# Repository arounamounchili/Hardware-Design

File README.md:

# Hardware-Design
All my PCB design projects

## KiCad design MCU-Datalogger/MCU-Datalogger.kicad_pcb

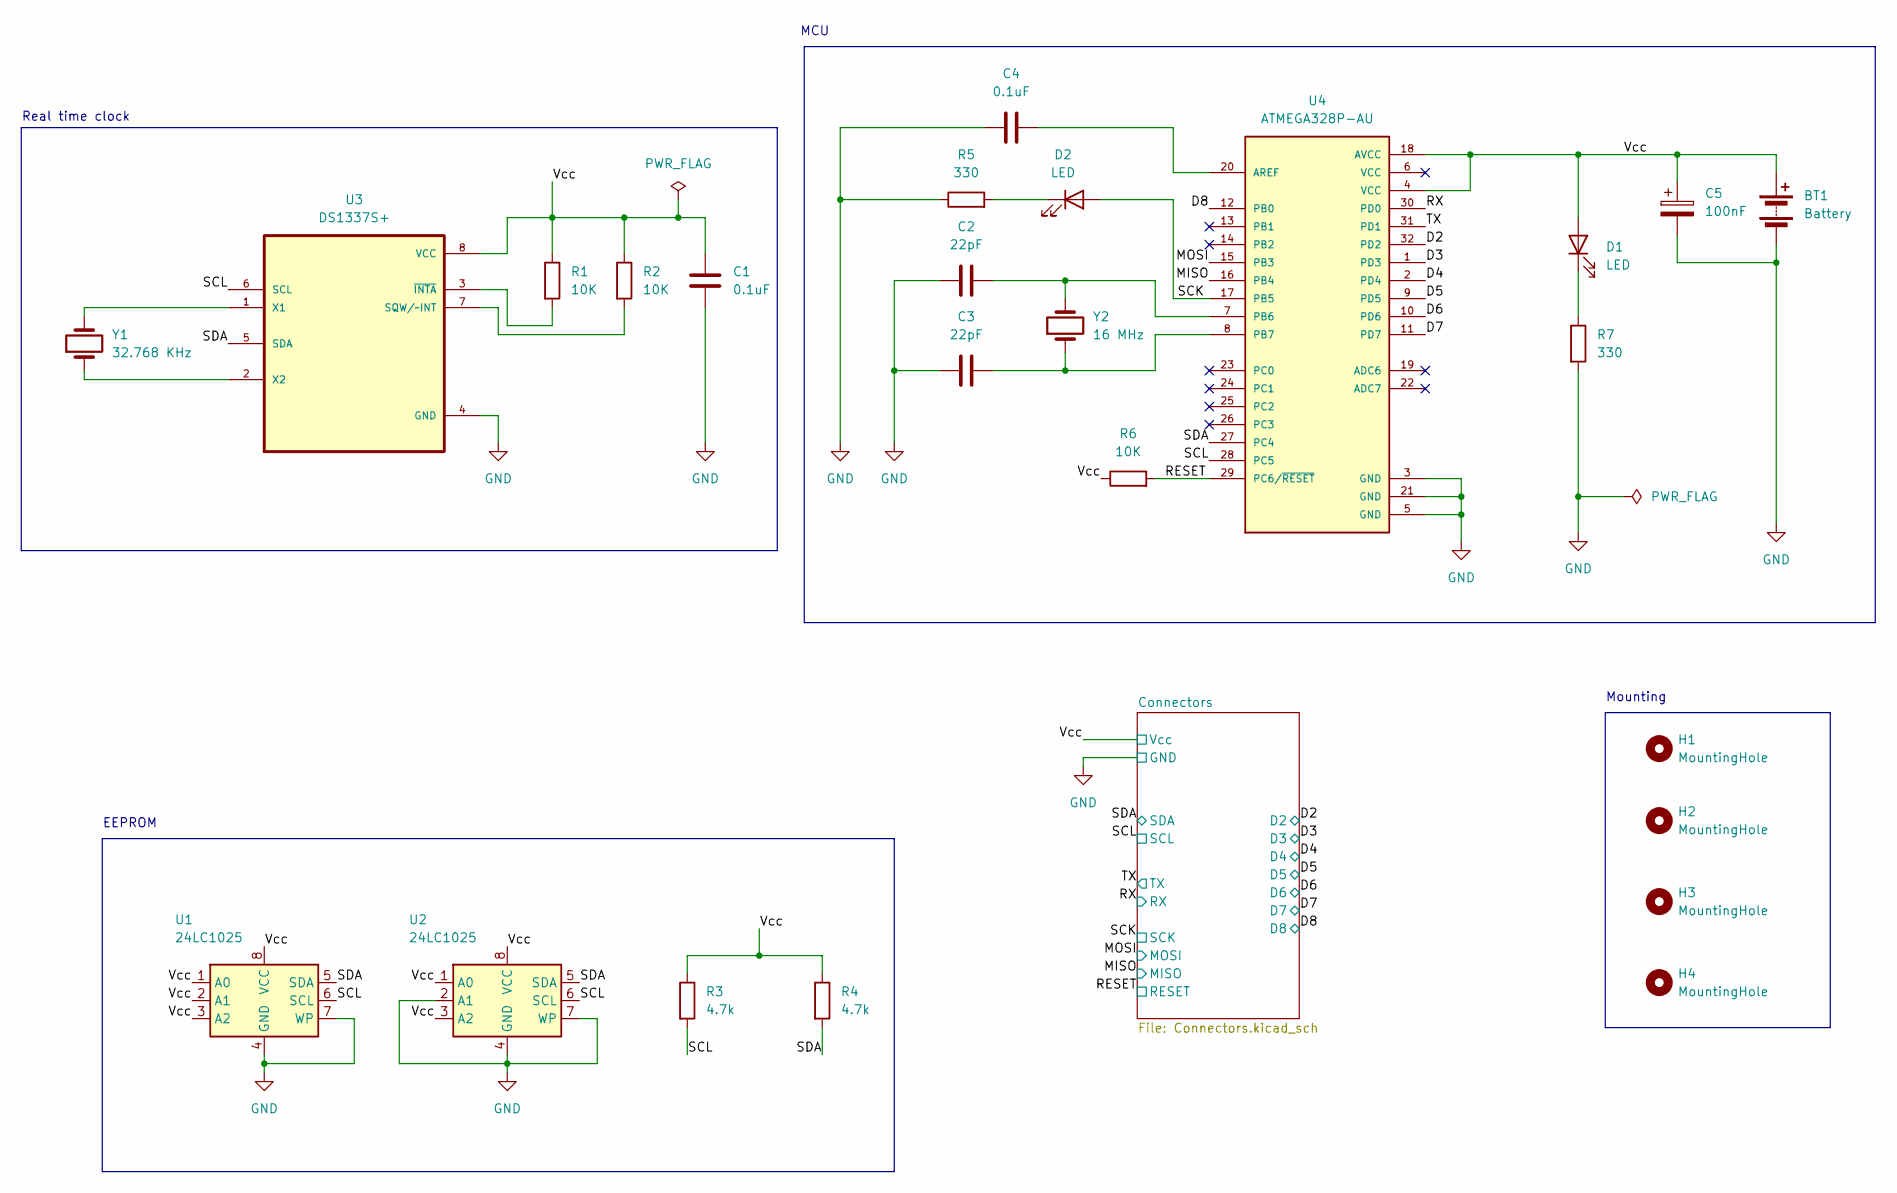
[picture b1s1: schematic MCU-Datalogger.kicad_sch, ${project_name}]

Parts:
BT1: Battery; PinHeader_1x02_P2.54mm_Vertical
C1, C4: 0.1uF; C_0805_2012Metric
C2, C3: 22pF; C_0805_2012Metric
C5: 100nF; C_0805_2012Metric
D1, D2: LED; LED_0805_2012Metric
H1, H2, H3, H4: MountingHole; MountingHole_2.1mm
R1, R2, R6: 10K; R_0805_2012Metric
R3, R4: 4.7k; R_0805_2012Metric
R5, R7: 330; R_0805_2012Metric
U1, U2: 24LC1025; SOIC-8_5.23x5.23mm_P1.27mm
U3: DS1337S+; SOIC127P600X175-8N
U4: ATMEGA328P-AU; QFP80P900X900X120-32N
Y1: 32.768 KHz; Crystal_SMD_5032-2Pin_5.0x3.2mm_HandSoldering
Y2: 16 MHz; Crystal_SMD_5032-2Pin_5.0x3.2mm_HandSoldering

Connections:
/D2: U4.32 (PD2); also elsewhere on the board
/D3: U4.1 (PD3); also elsewhere on the board
/D4: U4.2 (PD4); also elsewhere on the board
/D5: U4.9 (PD5); also elsewhere on the board
/D6: U4.10 (PD6); also elsewhere on the board
/D7: U4.11 (PD7); also elsewhere on the board
/D8: U4.12 (PB0); also elsewhere on the board
/MISO: U4.16 (PB4); also elsewhere on the board
/MOSI: U4.15 (PB3); also elsewhere on the board
/RESET: R6.2, U4.29 (PC6/~RESET); also elsewhere on the board
/RX: U4.30 (PD0); also elsewhere on the board
/SCK: D2.2 (A), U4.17 (PB5); also elsewhere on the board
/SCL: R3.2, U1.6 (SCL), U2.6 (SCL), U3.6 (SCL), U4.28 (PC5); also elsewhere on the board
/SDA: R4.2, U1.5 (SDA), U2.5 (SDA), U3.5 (SDA), U4.27 (PC4); also elsewhere on the board
/TX: U4.31 (PD1); also elsewhere on the board
/Vcc: BT1.1 (+), C1.2, C5.1, D1.2 (A), R1.1, R2.1, R3.1, R4.1, R6.1, U1.1 (A0), U1.2 (A1), U1.3 (A2), U1.8 (VCC), U2.1 (A0), U2.3 (A2), U2.8 (VCC), U3.8 (VCC), U4.4 (VCC), U4.18 (AVCC); also elsewhere on the board
GND: BT1.2 (-), C1.1, C2.1, C3.1, C4.1, C5.2, R5.1, R7.2, U1.4 (GND), U1.7 (WP), U2.2 (A1), U2.4 (GND), U2.7 (WP), U3.4 (GND), U4.3 (GND), U4.5 (GND), U4.21 (GND); also elsewhere on the board
unnamed: D1.1 (K), R7.1
unnamed: D2.1 (K), R5.2
unnamed: R2.2, U3.7 (SQW/~INT)
unnamed: U3.1 (X1), Y1.2
unnamed: U3.2 (X2), Y1.1
unnamed: R1.2, U3.3 (~INTA)
unnamed: C4.2, U4.20 (AREF)
unnamed: C2.2, U4.7 (PB6), Y2.2
unnamed: C3.2, U4.8 (PB7), Y2.1

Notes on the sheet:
EEPROM
Mounting
MCU
Real time clock

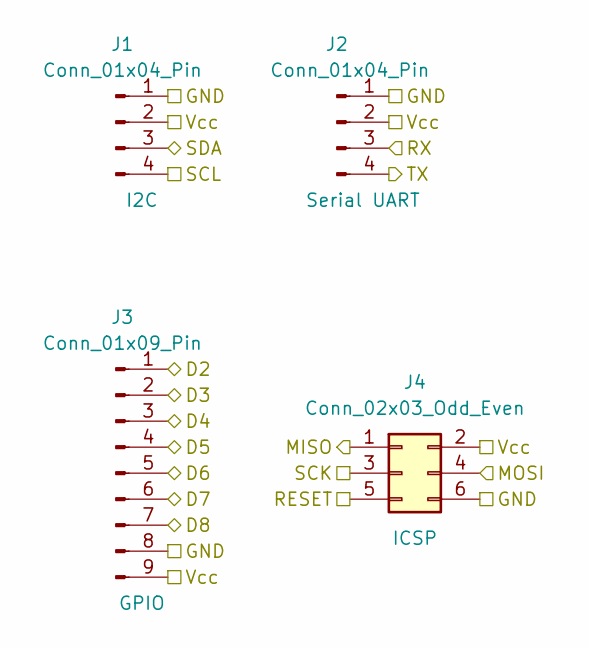
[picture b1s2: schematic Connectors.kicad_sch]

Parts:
J1, J2: Conn_01x04_Pin; PinHeader_1x04_P2.54mm_Vertical
J3: Conn_01x09_Pin; PinHeader_1x09_P2.54mm_Vertical
J4: Conn_02x03_Odd_Even; PinHeader_2x03_P2.54mm_Vertical

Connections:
/D2: J3.1; also elsewhere on the board
/D3: J3.2; also elsewhere on the board
/D4: J3.3; also elsewhere on the board
/D5: J3.4; also elsewhere on the board
/D6: J3.5; also elsewhere on the board
/D7: J3.6; also elsewhere on the board
/D8: J3.7; also elsewhere on the board
/MISO: J4.1; also elsewhere on the board
/MOSI: J4.4; also elsewhere on the board
/RESET: J4.5; also elsewhere on the board
/RX: J2.3; also elsewhere on the board
/SCK: J4.3; also elsewhere on the board
/SCL: J1.4; also elsewhere on the board
/SDA: J1.3; also elsewhere on the board
/TX: J2.4; also elsewhere on the board
/Vcc: J1.2, J2.2, J3.9, J4.2; also elsewhere on the board
GND: J1.1, J2.1, J3.8, J4.6; also elsewhere on the board

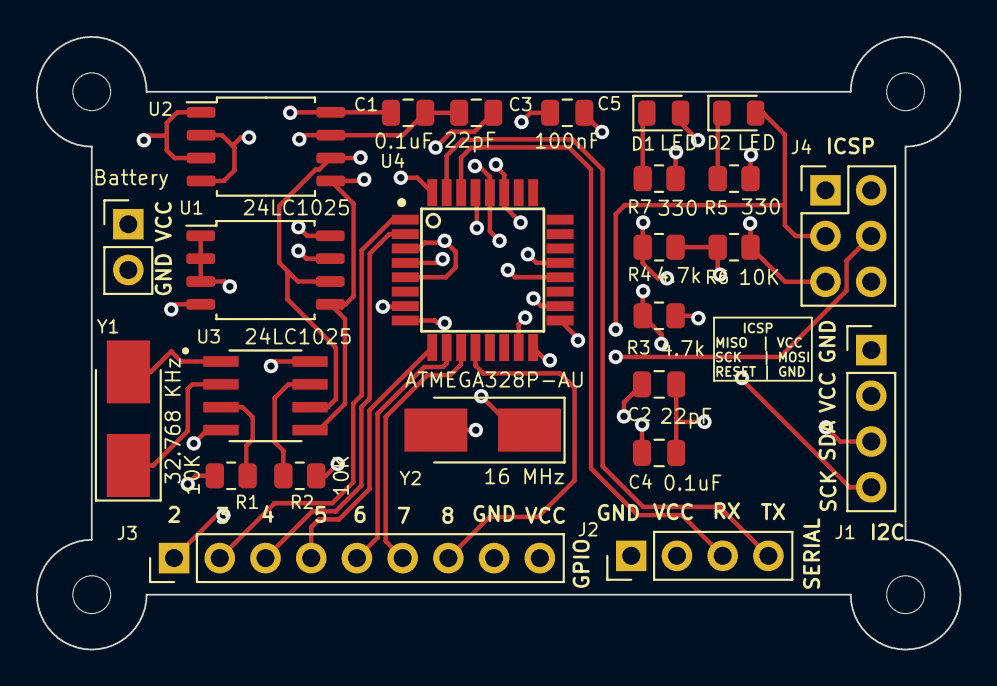
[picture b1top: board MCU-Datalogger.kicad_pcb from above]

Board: 4 copper layers, 51.3 x 34.0 mm, 29 parts (0 on the bottom side), 26 nets.

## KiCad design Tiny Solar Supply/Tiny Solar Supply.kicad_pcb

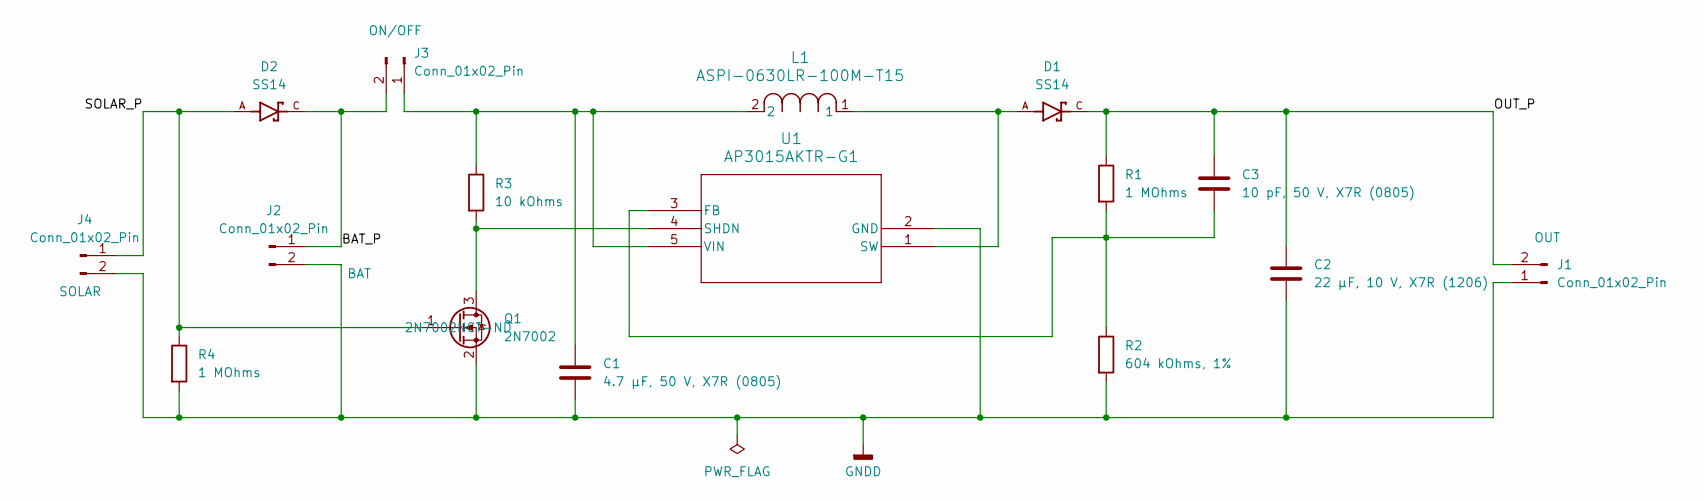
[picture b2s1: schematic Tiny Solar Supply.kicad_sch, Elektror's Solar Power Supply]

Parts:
C1: 4.7 µF, 50 V, X7R (0805); C_0805_2012Metric; Manufacturer Part Number 3372-0805N4R7B500ADTR-ND
C2: 22 µF, 10 V, X7R (1206); C_1206_3216Metric; Manufacturer Part Number 490-5309-1-ND
C3: 10 pF, 50 V, X7R (0805); C_0805_2012Metric; Manufacturer Part Number 3372-0805N100J101ADTR-ND
D1, D2: SS14; DIOM4325X250N; PARTREV O2102
J1, J2, J3: Conn_01x02_Pin; PinHeader_1x02_P2.54mm_Vertical
J4: Conn_01x02_Pin; PinHeader_1x02_P2.54mm_Horizontal
L1: ASPI-0630LR-100M-T15; IND_ASPI-0630LR_ABR; Manufacturer Part Number ASPI-0630LR-100M-T15
Q1: 2N7002; SOT-23; Manufacturer Part Number 2N7002NCT-ND
R1, R4: 1 MOhms; R_0805_2012Metric; Manufacturer Part Number RMCF0805FT1M00CT-ND
R2: 604 kOhms, 1%; R_0805_2012Metric; Manufacturer Part Number 738-RMCF0805FT604KCT-ND
R3: 10 kOhms; R_0805_2012Metric; Manufacturer Part Number RMCF0805FT10K0CT-ND
U1: AP3015AKTR-G1; SOT23-5_1P55X2P9_DIO; Manufacturer Part Number AP3015AKTR-G1DICT-ND

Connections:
/BAT_P: D2.C, J2.1, J3.2
/OUT_P: C2.1, C3.1, D1.C, J1.2, R1.1
/SOLAR_P: D2.A, J4.1, Q1.1 (G), R4.1
GNDD: C1.2, C2.2, J1.1, J2.2, J4.2, Q1.2 (S), R2.2, R4.2, U1.2 (GND)
unnamed: C1.1, J3.1, L1.2, R3.1, U1.5 (VIN)
unnamed: Q1.3 (D), R3.2, U1.4 (SHDN)
unnamed: C3.2, R1.2, R2.1, U1.3 (FB)
unnamed: D1.A, L1.1, U1.1 (SW)

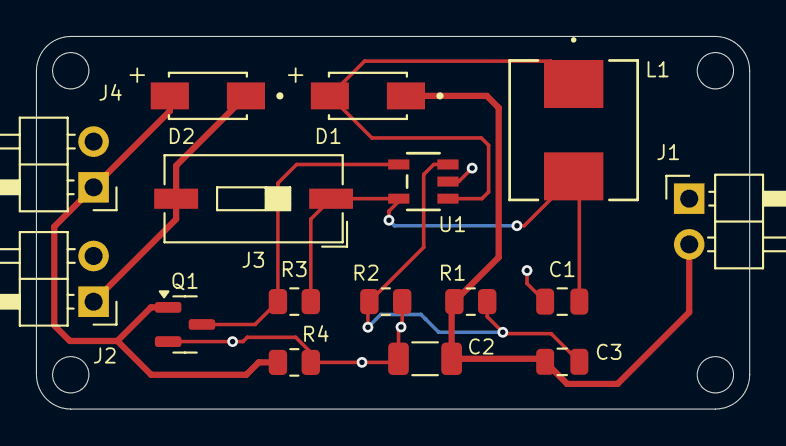
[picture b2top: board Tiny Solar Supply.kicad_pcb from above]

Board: 2 copper layers, 39.6 x 20.7 mm, 16 parts (0 on the bottom side), 8 nets.

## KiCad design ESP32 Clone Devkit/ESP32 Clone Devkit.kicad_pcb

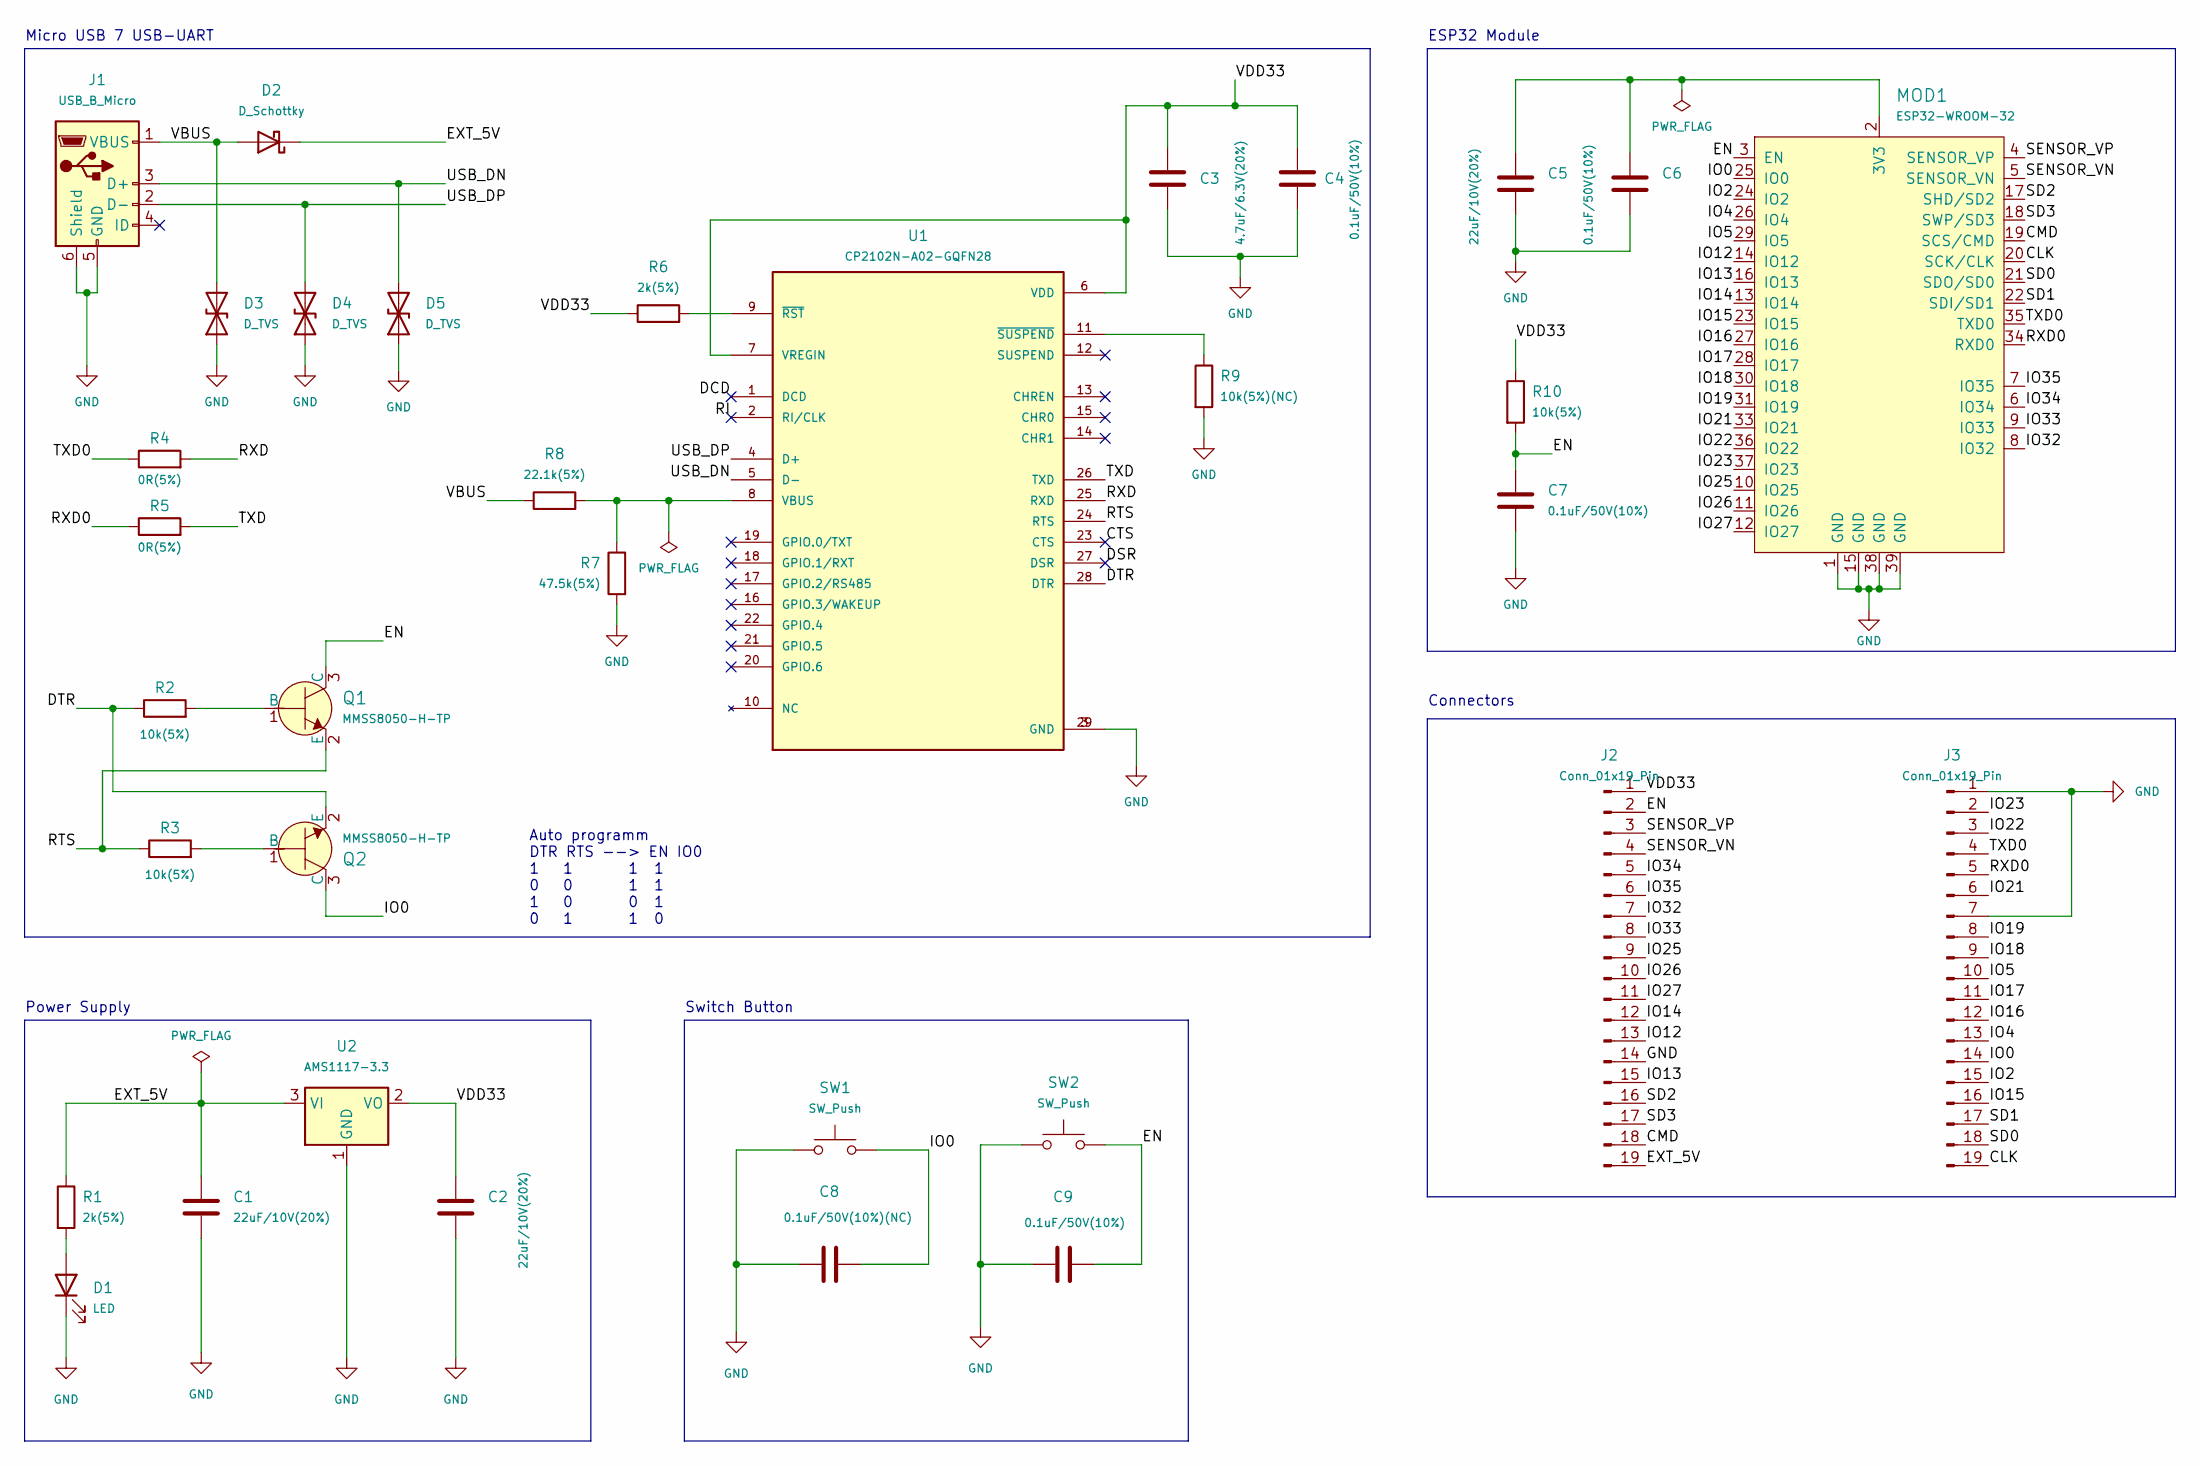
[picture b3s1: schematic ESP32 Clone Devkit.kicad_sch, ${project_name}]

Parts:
C1, C2, C5: 22uF/10V(20%); C_0201_0603Metric
C3: 4.7uF/6.3V(20%); C_01005_0402Metric
C4, C6, C7, C9: 0.1uF/50V(10%); C_01005_0402Metric
C8: 0.1uF/50V(10%)(NC); C_01005_0402Metric
D1: LED; LED_0603_1608Metric
D2: D_Schottky; D_SOD-323
D3, D4, D5: D_TVS; D_SOD-523
J1: USB_B_Micro; USB_Micro-AB_Molex_47590-0001
J2, J3: Conn_01x19_Pin; PinHeader_1x19_P2.54mm_Vertical
MOD1: ESP32-WROOM-32; ESP32-WROOM-32D; MPN ESP32-WROOM-32; Digi-Key_PN 1904-1010-1-ND
Q1, Q2: MMSS8050-H-TP; SOT-23-3; MPN MMSS8050-H-TP; Digi-Key_PN MMSS8050-H-TPMSCT-ND
R1, R6: 2k(5%); R_01005_0402Metric
R2, R3, R10: 10k(5%); R_01005_0402Metric
R4, R5: 0R(5%); R_01005_0402Metric
R7: 47.5k(5%); R_01005_0402Metric
R8: 22.1k(5%); R_01005_0402Metric
R9: 10k(5%)(NC); R_01005_0402Metric
SW1, SW2: SW_Push; SW_SPST_B3S-1000
U1: CP2102N-A02-GQFN28; TQFN-28-1EP_5x5mm_P0.5mm_EP2.7x2.7mm; PARTREV 1.5
U2: AMS1117-3.3; SOT-223-3_TabPin2

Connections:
/CLK: J3.19, MOD1.20 (SCK/CLK)
/CMD: J2.18, MOD1.19 (SCS/CMD)
/CTS: U1.23 (CTS)
/DCD: U1.1 (DCD)
/DSR: U1.27 (DSR)
/DTR: Q2.2 (E), R2.1, U1.28 (DTR)
/EN: C7.1, C9.2, J2.2, MOD1.3 (EN), Q1.3 (C), R10.2, SW2.2
/EXT_5V: C1.1, D2.1 (K), J2.19, R1.1, U2.3 (VI)
/IO0: C8.2, J3.14, MOD1.25 (IO0), Q2.3 (C), SW1.2
/IO2: J3.15, MOD1.24 (IO2)
/IO4: J3.13, MOD1.26 (IO4)
/IO5: J3.10, MOD1.29 (IO5)
/IO12: J2.13, MOD1.14 (IO12)
/IO13: J2.15, MOD1.16 (IO13)
/IO14: J2.12, MOD1.13 (IO14)
/IO15: J3.16, MOD1.23 (IO15)
/IO16: J3.12, MOD1.27 (IO16)
/IO17: J3.11, MOD1.28 (IO17)
/IO18: J3.9, MOD1.30 (IO18)
/IO19: J3.8, MOD1.31 (IO19)
/IO21: J3.6, MOD1.33 (IO21)
/IO22: J3.3, MOD1.36 (IO22)
/IO23: J3.2, MOD1.37 (IO23)
/IO25: J2.9, MOD1.10 (IO25)
/IO26: J2.10, MOD1.11 (IO26)
/IO27: J2.11, MOD1.12 (IO27)
/IO32: J2.7, MOD1.8 (IO32)
/IO33: J2.8, MOD1.9 (IO33)
/IO34: J2.5, MOD1.6 (IO34)
/IO35: J2.6, MOD1.7 (IO35)
/RI: U1.2 (RI/CLK)
/RTS: Q1.2 (E), R3.1, U1.24 (RTS)
/RXD: R4.2, U1.25 (RXD)
/RXD0: J3.5, MOD1.34 (RXD0), R5.1
/SD0: J3.18, MOD1.21 (SDO/SD0)
/SD1: J3.17, MOD1.22 (SDI/SD1)
/SD2: J2.16, MOD1.17 (SHD/SD2)
/SD3: J2.17, MOD1.18 (SWP/SD3)
/SENSOR_VN: J2.4, MOD1.5 (SENSOR_VN)
/SENSOR_VP: J2.3, MOD1.4 (SENSOR_VP)
/TXD: R5.2, U1.26 (TXD)
/TXD0: J3.4, MOD1.35 (TXD0), R4.1
/USB_DN: D5.2 (A2), J1.3 (D+), U1.5 (D-)
/USB_DP: D4.2 (A2), J1.2 (D-), U1.4 (D+)
/VBUS: D2.2 (A), D3.2 (A2), J1.1 (VBUS), R8.1
/VDD33: C2.1, C3.1, C4.1, J2.1, R6.1, R10.1, U1.6 (VDD), U1.7 (VREGIN), U2.2 (VO)
GND: C1.2, C2.2, C3.2, C4.2, C5.2, C6.2, C7.2, C8.1, C9.1, D1.1 (K), D3.1 (A1), D4.1 (A1), D5.1 (A1), J1.5 (GND), J1.6 (Shield), J2.14, J3.1, J3.7, MOD1.1 (GND), MOD1.15 (GND), MOD1.38 (GND), MOD1.39 (GND), R7.2, R9.2, SW1.1, SW2.1, U1.3 (GND), U1.29 (GND), U2.1 (GND)
unnamed: D1.2 (A), R1.2
unnamed: C5.1, C6.1, MOD1.2 (3V3)
unnamed: Q1.1 (B), R2.2
unnamed: Q2.1 (B), R3.2
unnamed: R7.1, R8.2, U1.8 (VBUS)
unnamed: R6.2, U1.9 (~RST)
unnamed: R9.1, U1.11 (~SUSPEND)

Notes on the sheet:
Connectors
Auto programm DTR RTS --> EN IO0 1 1 1 1 0 0 1 1 1 0 0 1 0 1 1 0
Micro USB 7 USB-UART
ESP32 Module
Switch Button
Power Supply

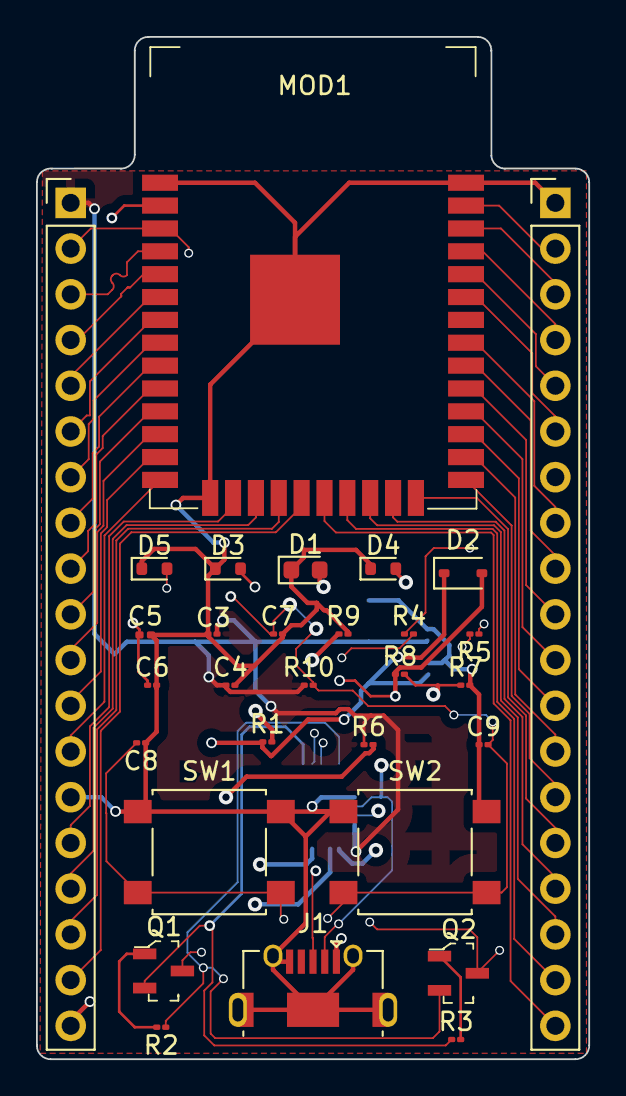
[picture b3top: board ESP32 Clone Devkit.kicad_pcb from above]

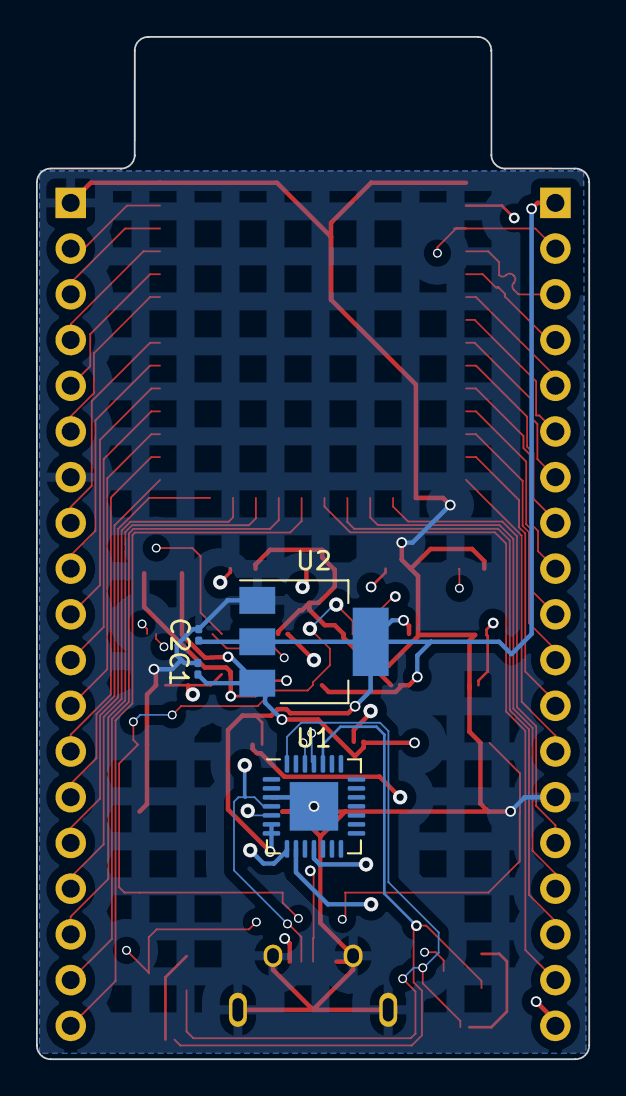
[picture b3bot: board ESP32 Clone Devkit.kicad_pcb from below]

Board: 4 copper layers, 30.7 x 56.8 mm, 34 parts (4 on the bottom side), 50 nets.

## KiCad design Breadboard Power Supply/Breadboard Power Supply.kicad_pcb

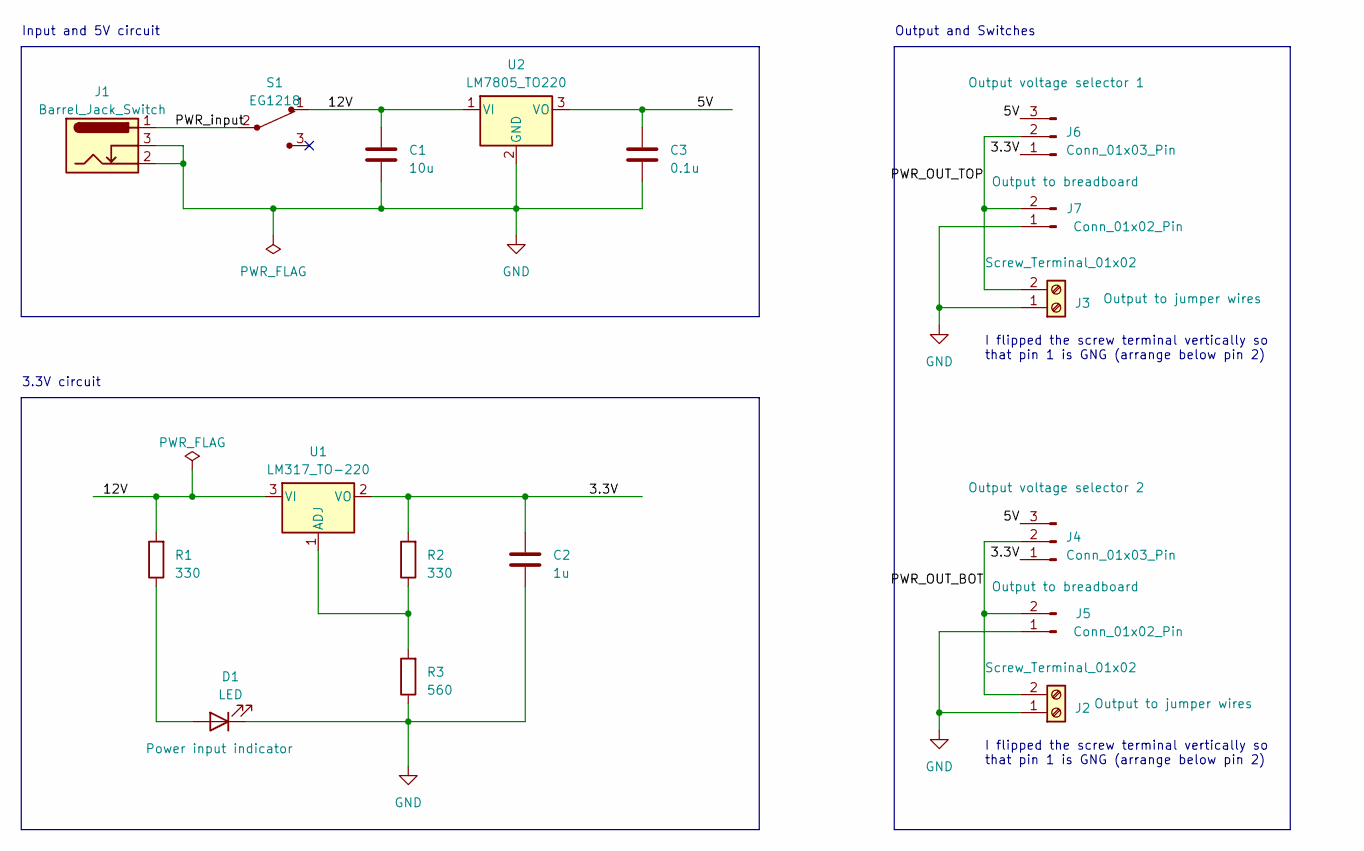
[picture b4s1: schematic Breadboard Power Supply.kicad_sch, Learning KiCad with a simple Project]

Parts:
C1: 10u; C_Disc_D3.0mm_W1.6mm_P2.50mm
C2: 1u; C_Disc_D3.0mm_W1.6mm_P2.50mm
C3: 0.1u; C_Disc_D3.0mm_W1.6mm_P2.50mm
D1: LED; LED_D5.0mm
J1: Barrel_Jack_Switch; BarrelJack_Horizontal
J2, J3: Screw_Terminal_01x02; TerminalBlock_bornier-2_P5.08mm
J4, J6: Conn_01x03_Pin; PinHeader_1x03_P2.54mm_Vertical
J5, J7: Conn_01x02_Pin; PinHeader_1x02_P2.54mm_Vertical
R1, R2: 330; R_Axial_DIN0204_L3.6mm_D1.6mm_P7.62mm_Horizontal
R3: 560; R_Axial_DIN0204_L3.6mm_D1.6mm_P7.62mm_Horizontal
S1: EG1218; Switch_Slide_11.6x4mm_EG1218; MPN EG1218; Digi-Key_PN EG1903-ND
U1: LM317_TO-220; TO-220-3_Vertical
U2: LM7805_TO220; TO-220-3_Vertical

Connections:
/3.3V: C2.1, J4.1, J6.1, R2.2, U1.2 (VO)
/5V: C3.1, J4.3, J6.3, U2.3 (VO)
/12V: C1.1, R1.2, S1.1, U1.3 (VI), U2.1 (VI)
/PWR_OUT_BOT: J2.2, J4.2, J5.2
/PWR_OUT_TOP: J3.2, J6.2, J7.2
/PWR_input: J1.1, S1.2
GND: C1.2, C2.2, C3.2, D1.1 (K), J1.2, J1.3, J2.1, J3.1, J5.1, J7.1, R3.1, U2.2 (GND)
unnamed: D1.2 (A), R1.1
unnamed: R2.1, R3.2, U1.1 (ADJ)

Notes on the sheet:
Output and Switches
3.3V circuit
Input and 5V circuit
I flipped the screw terminal vertically so that pin 1 is GNG (arrange below pin 2)

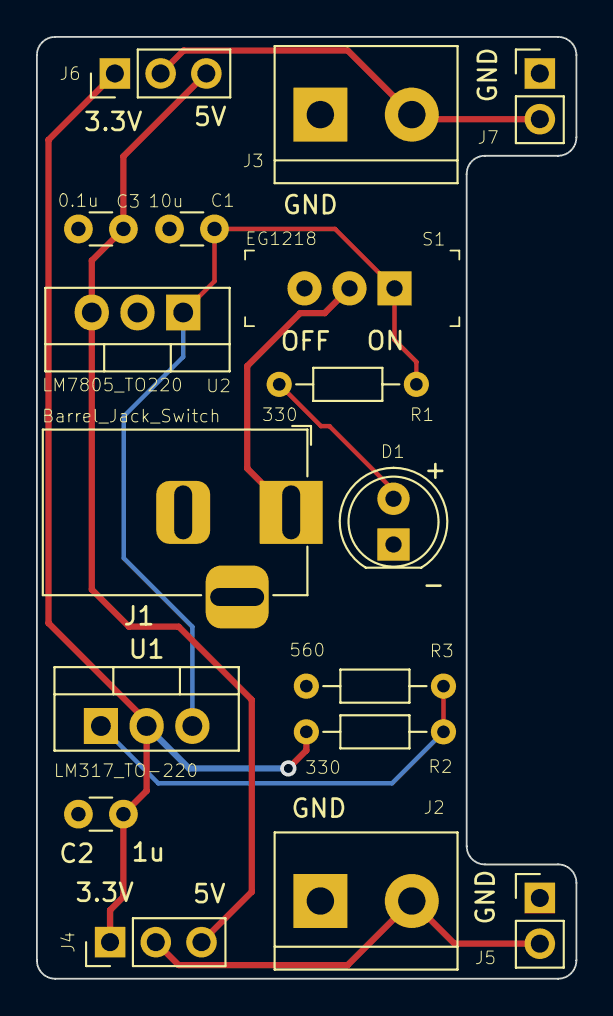
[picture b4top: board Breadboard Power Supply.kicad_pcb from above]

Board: 2 copper layers, 30.0 x 52.3 mm, 17 parts (0 on the bottom side), 9 nets.

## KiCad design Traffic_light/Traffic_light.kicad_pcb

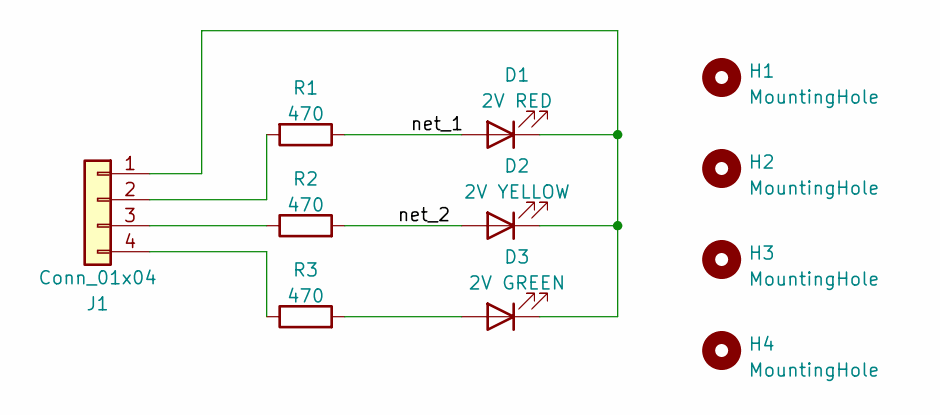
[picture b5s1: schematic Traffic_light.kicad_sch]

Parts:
D1: 2V RED; LED_D3.0mm
D2: 2V YELLOW; LED_D3.0mm
D3: 2V GREEN; LED_D3.0mm
H1, H2, H3, H4: MountingHole; MountingHole_2.5mm_Pad
J1: Conn_01x04; PinHeader_1x04_P2.54mm_Horizontal
R1, R2, R3: 470; R_Axial_DIN0204_L3.6mm_D1.6mm_P5.08mm_Horizontal

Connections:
/net_1: D1.2 (A), R1.1
/net_2: D2.2 (A), R2.2
unnamed: D1.1 (K), D2.1 (K), D3.1 (K), J1.1
unnamed: D3.2 (A), R3.2
unnamed: J1.2, R1.2
unnamed: J1.3, R2.1
unnamed: J1.4, R3.1

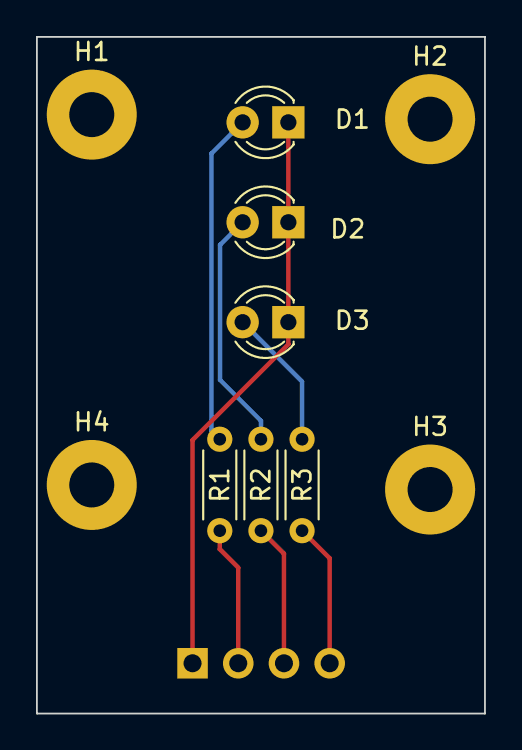
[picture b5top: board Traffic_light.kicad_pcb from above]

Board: 2 copper layers, 24.9 x 37.6 mm, 11 parts (1 on the bottom side), 7 nets.

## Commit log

2023-07-10 First commit of new Project
2023-07-10 Create Gebers folders
2023-07-10 add comment
2023-07-10 Do not sent Gebers folders to repo
2023-07-10 Stup of EEschema for new project
2023-07-10 have added required symbol to the schematic sheets
2023-07-10 arrange sysmbols in the schematic
2023-07-11 Edit component values
2023-07-11 Associate footprints with symbols
2023-07-11 remove auto_saved_files for: do not send it to repo
2023-07-11 Wriring on scheet1
2023-07-11 Wriring the second scheet
2023-07-11 Allocated Vcc and GND nets to the Power net class
2023-07-11 add comments to eeschema
2023-07-12 Setup pcbnew
2023-07-12 Added Outline in Edge.Cuts
2023-07-13 Place components
2023-07-13 Refine outline
2023-07-14 Roututing
2023-07-14 refine silkscreen
2023-07-14 fixed outstanding issues
2023-07-14 generate gebers files
2023-07-14 2 Layer PCB completed
2023-07-15 modified SCL to SCK Label because of wrong pin was choosen
2023-07-15 complet 2Layer pcb
2023-07-15 change file name
2023-07-16 do not send Libraries folder
2023-07-16 Delete MCU-Datalogger/Libraries directory
    Delete folder
2023-07-20 finish 4 Layer design
2023-07-20 gitattributes file added to ignore PCB files during merge.
2023-07-21 Traffic_light project is added
2023-07-25 Power Supply project is added
2023-07-25 first init
2023-07-25 add symbols
2023-07-25 Annotate and set components values
2023-07-25 rename folder
2023-07-26 arange components in schematic
2023-07-26 associate footprints to symbols
2023-07-27 terminate wiring
2023-07-27 add nets Classes
2023-07-27 add comments
2023-07-28 mark unused pins
2023-07-28 Define pcb outline size and shape
2024-12-01 add new project
2024-12-01 Tiny Solar Supply project
2024-12-01 Update project
2024-12-30 Project for STM32L432KBU6 Microntroller - RF and USB
2025-01-05 Create a Project
